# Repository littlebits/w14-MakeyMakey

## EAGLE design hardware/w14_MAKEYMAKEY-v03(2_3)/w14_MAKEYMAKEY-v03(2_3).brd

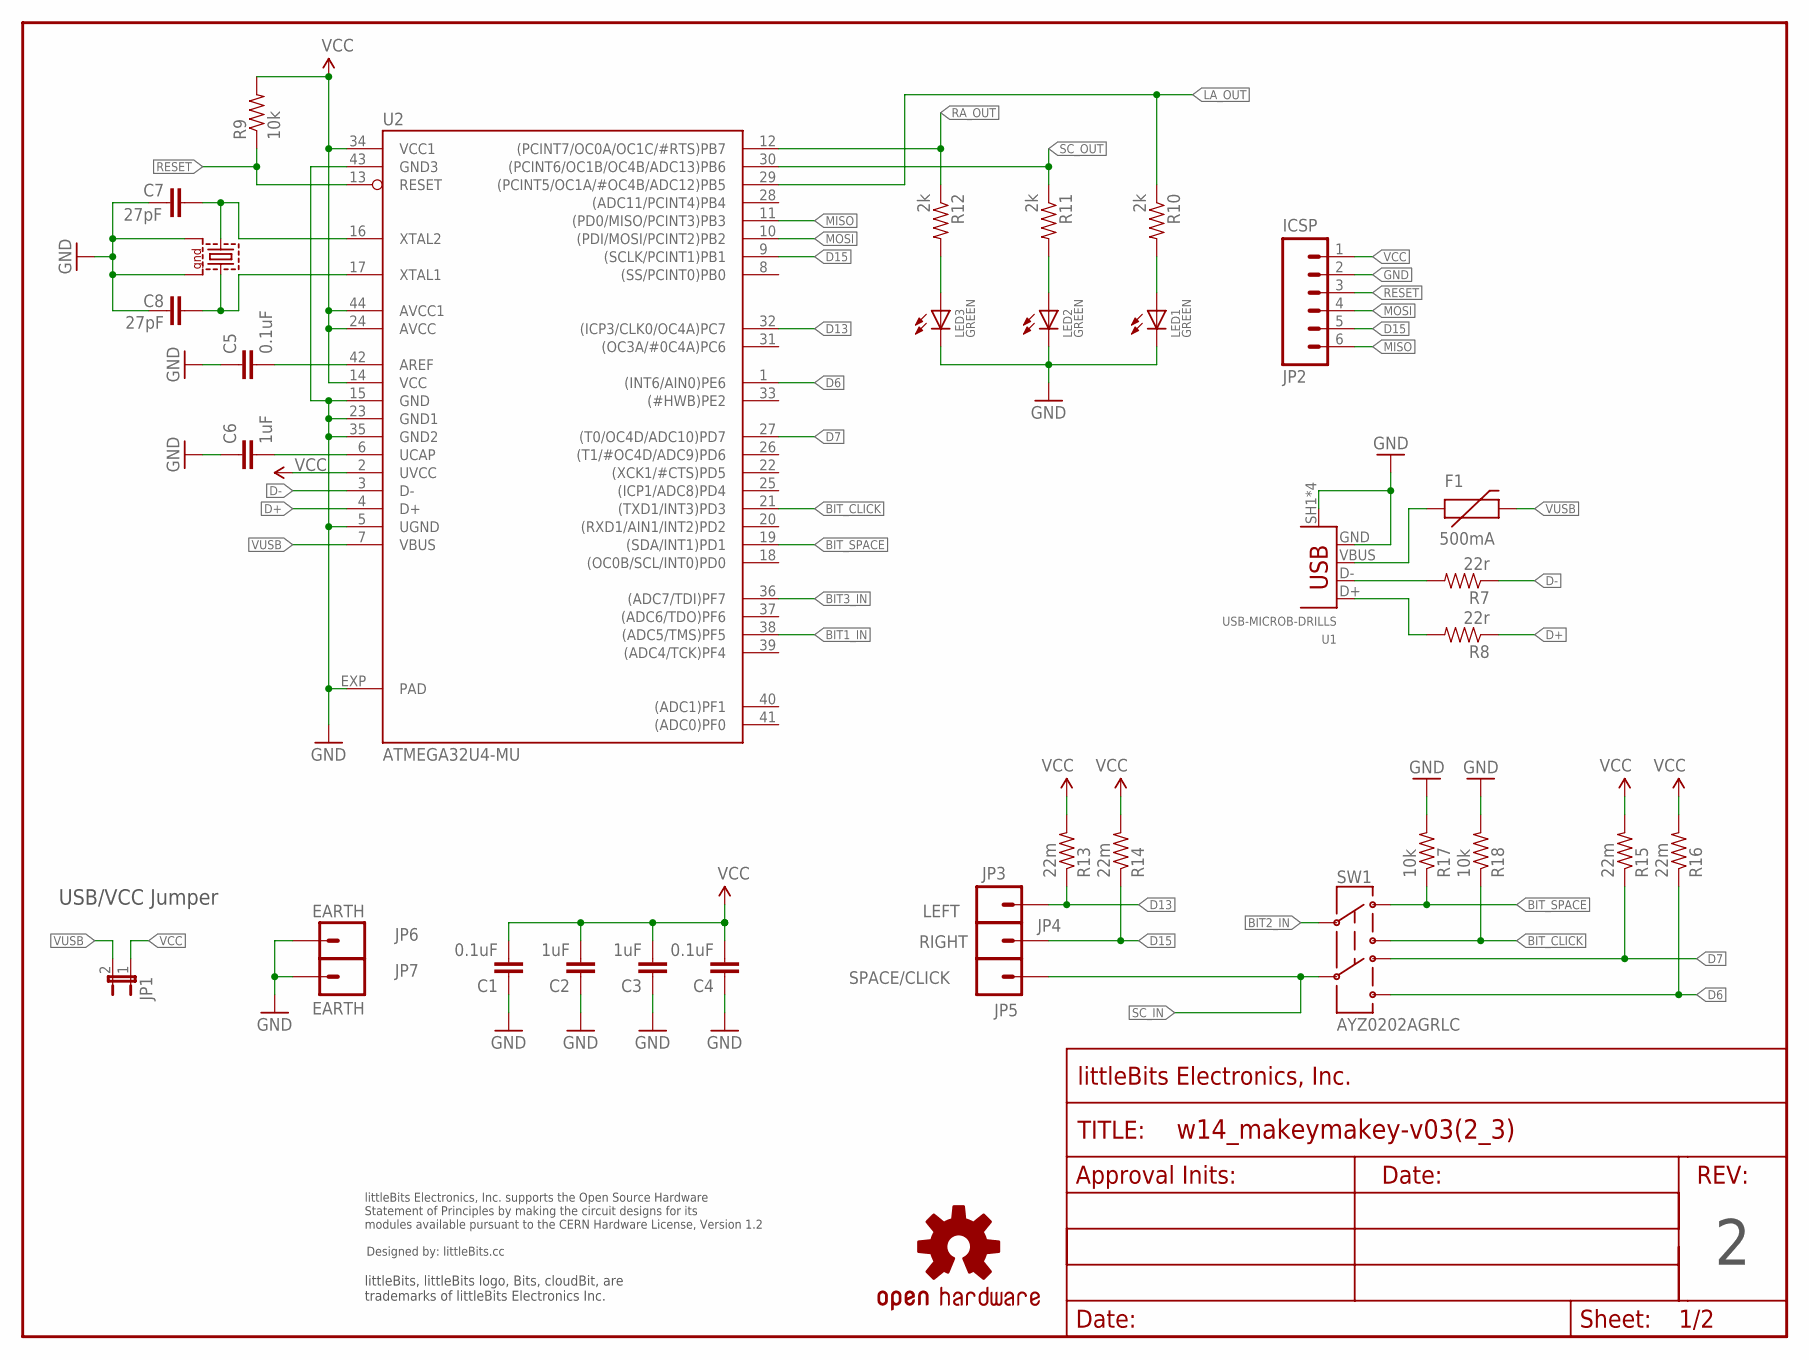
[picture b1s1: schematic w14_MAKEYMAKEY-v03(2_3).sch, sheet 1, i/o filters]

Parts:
C1, C4, C5: 0.1uF; CAP-0603
C2, C3, C6: 1uF; CAP-0603
C7, C8: 27pF; CAP-0603
F1: 500mA; PTC-1206
JP1: JUMPER-2SMD-NO; SJ_2S-NO
JP2: ICSP; SIP6-SM-0.1IN-NOS.S.
JP3: LEFT; 1X01_ALLIGATOR_3MM
JP4: RIGHT; 1X01_ALLIGATOR_3MM
JP5: SPACE/CLICK; 1X01_ALLIGATOR_3MM
JP6, JP7: EARTH; 1X01_ALLIGATOR_3MM
LED1, LED2, LED3: GREEN; LED-1206
Q1: 16MHz; CRYSTAL-SMD-7B-SERIES-5X3.2MM
R7, R8: 22r; RES-0603
R9, R17, R18: 10k; RES-0603
R10, R11, R12: 2k; RES-0603
R13, R14, R15, R16: 22m; RES-0603
SW1: AYZ0202AGRLC; AYZ0202
U1: USB-MICROB-DRILLS; USB-MICROB-AUK-DRILLS
U2: ATMEGA32U4-MU; QFN44ML7X7
U$1: OSHWCREDIT
U$58: FRAME-LETTER-OHWOHW; FABDWG01-OHW
U$70: OSHW-LOGOL; OSHW-LOGO-L

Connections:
BIT1_IN: U2.38 ((ADC5/TMS)PF5); also elsewhere on the board
BIT2_IN: SW1.2; also elsewhere on the board
BIT3_IN: U2.36 ((ADC7/TDI)PF7); also elsewhere on the board
BIT_CLICK: R18.1, SW1.3, U2.21 ((TXD1/INT3)PD3)
BIT_SPACE: R17.1, SW1.1, U2.19 ((SDA/INT1)PD1)
D6: R16.1, SW1.6, U2.1 ((INT6/AIN0)PE6)
D7: R15.1, SW1.4, U2.27 ((T0/OC4D/ADC10)PD7)
D13: JP3.1@0, JP3.1@2, R13.1, U2.32 ((ICP3/CLK0/OC4A)PC7)
D15: JP2.5, JP4.1@0, JP4.1@2, R14.1, U2.9 ((SCLK/PCINT1)PB1)
D+: R8.1, U2.4 (D+)
D-: R7.1, U2.3 (D-)
GND: C1.1, C2.1, C3.2, C4.1, C5.1, C6.1, C7.2, C8.2, JP2.2, JP6.1@0, JP6.1@2, JP7.1@0, JP7.1@2, LED1.C, LED2.C, LED3.C, Q1.P$2 (2), Q1.P$4 (4), R17.2, R18.2, U1.GND, U1.SH1 (SH), U1.SH2 (SH), U1.SH3 (SH), U1.SH4 (SH), U2.5 (UGND), U2.15 (GND), U2.23 (GND1), U2.35 (GND2), U2.43 (GND3), U2.EXP (PAD); also elsewhere on the board
LA_OUT: R10.1, U2.29 ((PCINT5/OC1A/#OC4B/ADC12)PB5); also elsewhere on the board
MISO: JP2.6, U2.11 ((PD0/MISO/PCINT3)PB3)
MOSI: JP2.4, U2.10 ((PDI/MOSI/PCINT2)PB2)
unnamed: LED3.A, R12.2
unnamed: LED1.A, R10.2
unnamed: LED2.A, R11.2
unnamed: C5.2, U2.42 (AREF)
unnamed: C7.1, Q1.P$3 (3), U2.16 (XTAL2)
unnamed: R7.2, U1.D-
unnamed: R8.2, U1.D+
unnamed: F1.1, U1.VBUS
unnamed: C8.1, Q1.P$1 (1), U2.17 (XTAL1)
unnamed: C6.2, U2.6 (UCAP)
RA_OUT: R12.1, U2.12 ((PCINT7/OC0A/OC1C/#RTS)PB7); also elsewhere on the board
RESET: JP2.3, R9.1, U2.13 (RESET)
SC_IN: JP5.1@0, JP5.1@2, SW1.5
SC_OUT: R11.1, U2.30 ((PCINT6/OC1B/OC4B/ADC13)PB6); also elsewhere on the board
VCC: C1.2, C2.2, C3.1, C4.2, JP1.1, JP2.1, R9.2, R13.2, R14.2, R15.2, R16.2, U2.2 (UVCC), U2.14 (VCC), U2.24 (AVCC), U2.34 (VCC1), U2.44 (AVCC1); also elsewhere on the board
VUSB: F1.2, JP1.2, U2.7 (VBUS)

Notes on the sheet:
USB/VCC Jumper

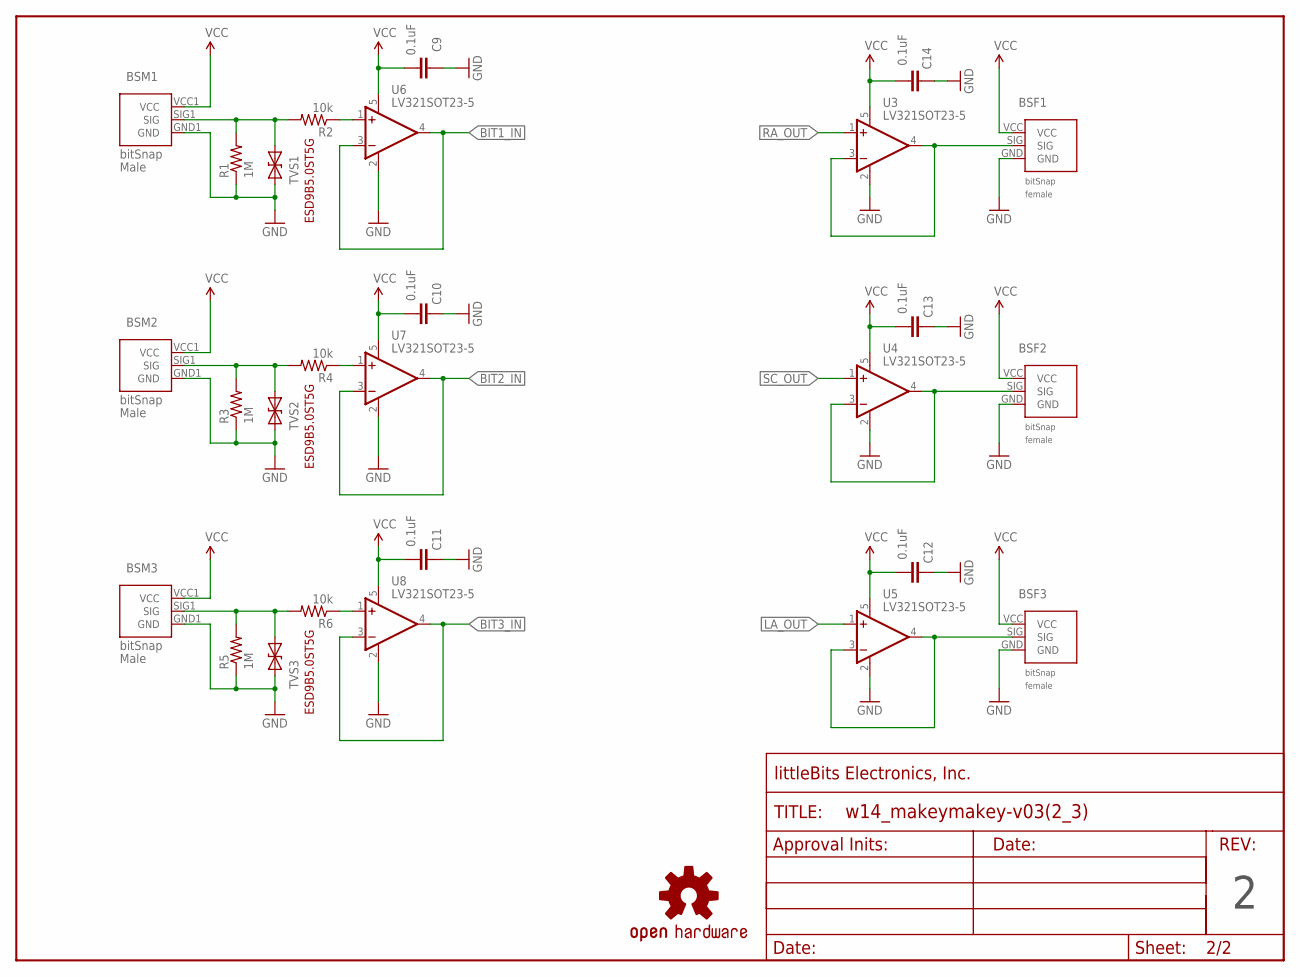
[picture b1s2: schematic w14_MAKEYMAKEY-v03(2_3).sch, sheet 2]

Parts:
BSF1, BSF2, BSF3: BITSNAP_V03_FEMALE
BSM1, BSM2, BSM3: BITSNAP_V03_MALE
C9, C10, C11, C12, C13, C14: 0.1uF; CAP-0603
R1, R3, R5: 1M; RES-0603
R2, R4, R6: 10k; RES-0603
TVS1, TVS2, TVS3: ESD9B5.0ST5G; SOD-923
U3, U4, U5, U6, U7, U8: LV321SOT23-5; SOT23-5
U$2: FRAME-LETTER-OHWOHW; FABDWG01-OHW
U$56: OSHW-LOGOL; OSHW-LOGO-L

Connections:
BIT1_IN: U6.3 (-IN), U6.4 (OUT); also elsewhere on the board
BIT2_IN: U7.3 (-IN), U7.4 (OUT); also elsewhere on the board
BIT3_IN: U8.3 (-IN), U8.4 (OUT); also elsewhere on the board
GND: BSF1.GND, BSF2.GND, BSF3.GND, BSM1.GND1 (GND), BSM2.GND1 (GND), BSM3.GND1 (GND), C9.1, C10.1, C11.1, C12.1, C13.1, C14.1, R1.1, R3.1, R5.1, TVS1.1 (A), TVS2.1 (A), TVS3.1 (A), U3.2 (V-), U4.2 (V-), U5.2 (V-), U6.2 (V-), U7.2 (V-), U8.2 (V-); also elsewhere on the board
LA_OUT: U5.1 (+IN); also elsewhere on the board
unnamed: R4.1, U7.1 (+IN)
unnamed: R2.1, U6.1 (+IN)
unnamed: R6.1, U8.1 (+IN)
RA_OUT: U3.1 (+IN); also elsewhere on the board
SC_OUT: U4.1 (+IN); also elsewhere on the board
SIG1_IN: BSM1.SIG1 (SIG), R1.2, R2.2, TVS1.2 (C)
SIG1_OUT: BSF1.SIG, U3.3 (-IN), U3.4 (OUT)
SIG2_IN: BSM2.SIG1 (SIG), R3.2, R4.2, TVS2.2 (C)
SIG2_OUT: BSF2.SIG, U4.3 (-IN), U4.4 (OUT)
SIG3_IN: BSM3.SIG1 (SIG), R5.2, R6.2, TVS3.2 (C)
SIG3_OUT: BSF3.SIG, U5.3 (-IN), U5.4 (OUT)
VCC: BSF1.VCC, BSF2.VCC, BSF3.VCC, BSM1.VCC1 (VCC), BSM2.VCC1 (VCC), BSM3.VCC1 (VCC), C9.2, C10.2, C11.2, C12.2, C13.2, C14.2, U3.5 (V+), U4.5 (V+), U5.5 (V+), U6.5 (V+), U7.5 (V+), U8.5 (V+); also elsewhere on the board

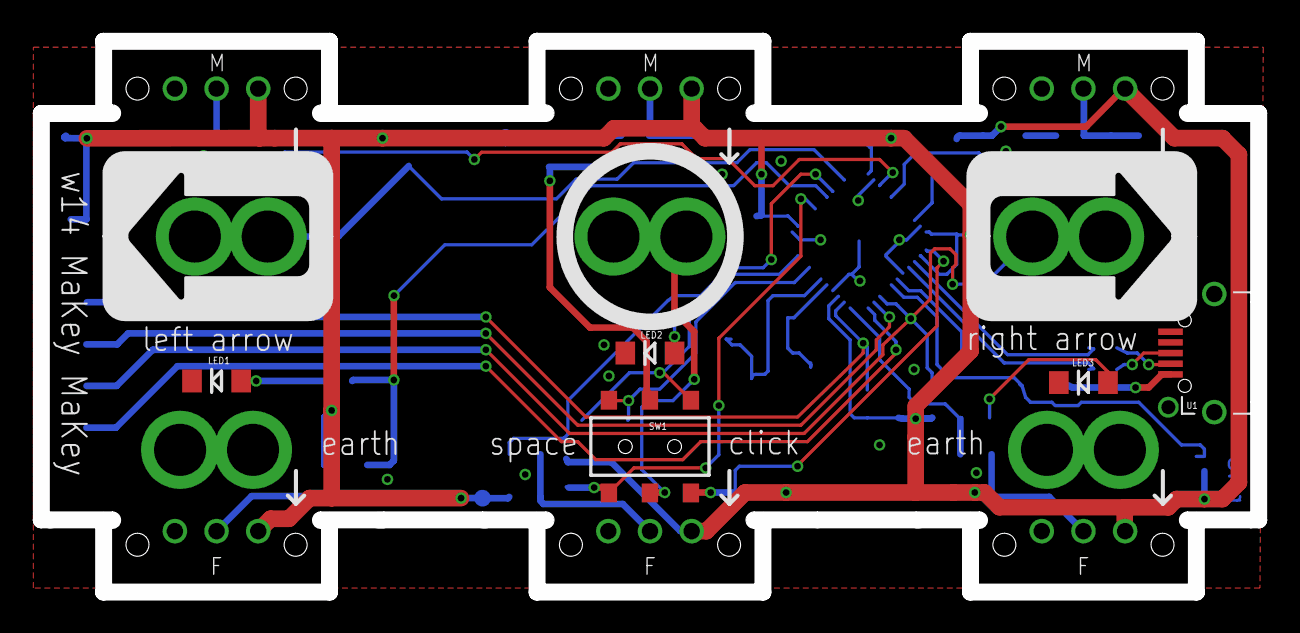
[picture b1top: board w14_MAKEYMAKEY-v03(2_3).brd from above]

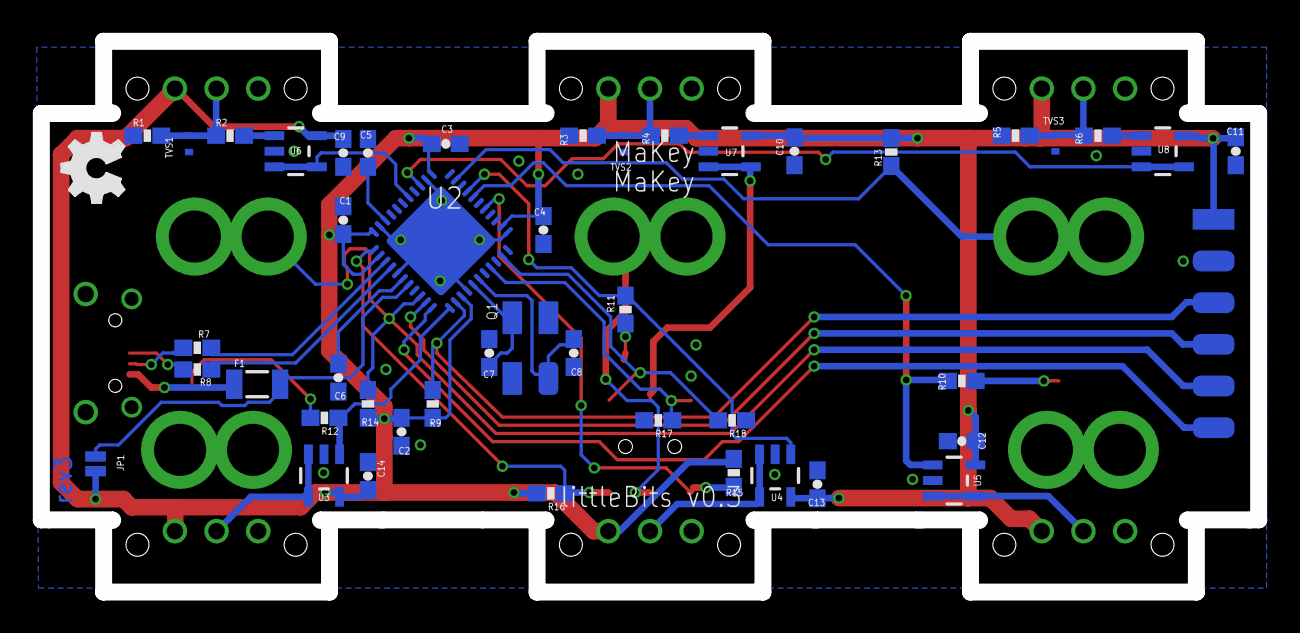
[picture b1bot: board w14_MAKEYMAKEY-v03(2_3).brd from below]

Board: 2 copper layers, 74.2 x 33.6 mm, 68 parts (46 on the bottom side), 40 nets.

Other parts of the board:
U$5: OSHW_FILLX150_NOTEXT

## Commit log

2015-04-21 First commit, added hardware and firmware

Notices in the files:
parts and their libraries:
LITTLEBITS: modules available pursuant to the CERN Hardware License,
Version 1.2
SparkFun-Connectors: Licensing: CC v3.0 Share-Alike You are welcome to use this library for commercial purposes.
LITTLEBITS: modules available pursuant to the CERN Hardware License, Version 1.2
